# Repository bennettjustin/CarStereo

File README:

Working on writing a detailed README... until then here are some of my ramblings.

## Stereo Project Thoughts
Need to set up organization for project(s)
List of Projects:
- PCBs - group as single repo, ~~single kicad project~~, multiple projects bc messy w/ multiple sheets
	- Audio
	- Main (Raspberry Pi carrier)
	- Power (Car communications)
- CarPlay
	- react-carplay - will be using this initially
	- carplay-rs - in very initial stage of development
- CAD
	- Malibu Stereo faceplate for RPi touchscreen
	- Malibu Stereo adapter for better touchscreen

Order of prioritization
1. PCB - Power
2. PCB - Audio
3. CAD - Faceplate
4. CarPlay (working on getting rpi booting up to react-carplay first)

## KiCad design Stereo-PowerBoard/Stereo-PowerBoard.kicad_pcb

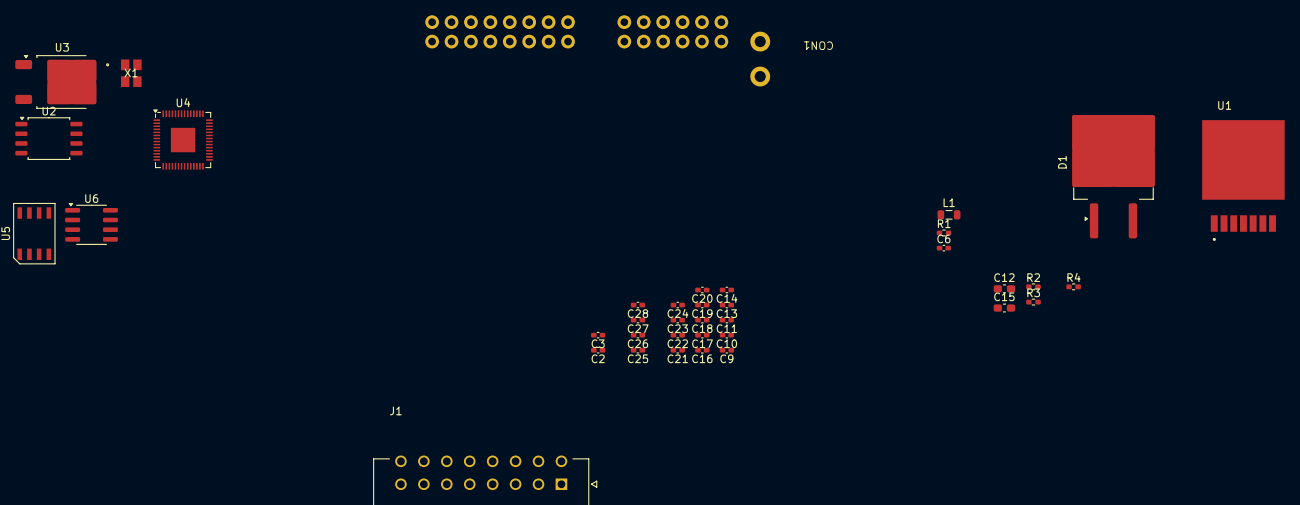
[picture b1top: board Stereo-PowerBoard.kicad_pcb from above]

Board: 2 copper layers, 38 parts (0 on the bottom side), 28 nets, no tracks yet.

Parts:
C2: 1n; C_0402_1005Metric_Pad0.74x0.62mm_HandSolder
C3: 0.01u; C_0402_1005Metric_Pad0.74x0.62mm_HandSolder
C6: 0.47u; C_0402_1005Metric_Pad0.74x0.62mm_HandSolder
C9, C10, C13, C17, C18, C19, C20, C21, C22, C23: 100n; C_0402_1005Metric_Pad0.74x0.62mm_HandSolder
C11, C16: 15p; C_0402_1005Metric_Pad0.74x0.62mm_HandSolder
C12, C15: 10u; C_0603_1608Metric_Pad1.08x0.95mm_HandSolder
C14, C24, C25, C27, C28: 1u; C_0402_1005Metric_Pad0.74x0.62mm_HandSolder
C26: 220p; C_0402_1005Metric_Pad0.74x0.62mm_HandSolder
CON1: Connector Body Harness
D1: 6TQ045S; TO-263-2
J1: 430451600; MOLEX_430451600
L1: 22u; L_0805_2012Metric
R1: 5.6k; R_0402_1005Metric_Pad0.72x0.64mm_HandSolder
R2: R; R_0402_1005Metric_Pad0.72x0.64mm_HandSolder
R3: 1k; R_0402_1005Metric_Pad0.72x0.64mm_HandSolder
R4: 4k7; R_0402_1005Metric_Pad0.72x0.64mm_HandSolder
U1: LM2679SX-5.0_NOPB; VREG_LM2679SX-5.0_NOPB
U2: W25Q32JVSS; SOIC-8_5.23x5.23mm_P1.27mm
U3: NCP1117-3.3_TO252; TO-252-2
U4: RP2040; QFN-56-1EP_7x7mm_P0.4mm_EP3.2x3.2mm
U5: TLIN1027; SOIC-8
U6: TJA1051T-3; SOIC-8_3.9x4.9mm_P1.27mm
X1: ABM8-272-T3; ABM8-272-T3_ABR

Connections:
+1V1: C9.1, C13.1, C14.1, U4.23 (DVDD), U4.45 (VREG_VOUT), U4.50 (DVDD)
+3V3: C10.1, C15.1, C17.1, C18.1, C19.1, C20.1, C21.1, C22.1, C23.1, C24.1, C28.1, R2.1, R4.1, U2.8 (VCC), U3.2 (VO), U4.1 (IOVDD), U4.10 (IOVDD), U4.22 (IOVDD), U4.33 (IOVDD), U4.42 (IOVDD), U4.43 (ADC_AVDD), U4.44 (VREG_IN), U4.48 (USB_VDD), U4.49 (IOVDD), U6.5 (VIO)
+BATT: C6.1, C25.1, CON1.X1.1 (V_BAT), U1.2 (INPUT), U5.7 (VSUP)
GMLAN: CON1.X1.9 (GMLAN), CON1.X1.10 (GMLAN), U6.7 (CANH)
GND: C2.2, C6.2, C9.2, C10.2, C11.2, C12.2, C13.2, C14.2, C15.2, C16.2, C17.2, C18.2, C19.2, C20.2, C21.2, C22.2, C23.2, C24.2, C25.2, C26.2, C27.2, C28.2, CON1.X1.8 (GND), D1.2 (A), R1.2, U1.4 (GND), U1.8 (DAP), U2.4 (GND), U3.1 (GND), U4.19 (TESTEN), U4.57 (GND), U5.5 (GND), U6.2 (GND), U6.6 (CANL), X1.2, X1.4
LIN: C26.1, U5.6 (LIN)
LIN_RXD: R4.2, U5.1 (RXD)
unnamed: C16.1, R3.1, X1.3
unnamed: R1.1, U1.5 (CURRENT_ADJUST)
unnamed: C2.1, U1.7 (SS)
QSPI_SCLK: U2.6 (CLK), U4.52 (QSPI_SCLK)
QSPI_SD0: U2.5 (DI(IO0)), U4.53 (QSPI_SD0)
QSPI_SD1: U2.2 (DO(IO1)), U4.55 (QSPI_SD1)
QSPI_SD2: U2.3 (IO2), U4.54 (QSPI_SD2)
QSPI_SD3: U2.7 (IO3), U4.51 (QSPI_SD3)
QSPI_SS: R2.2, U2.1 (~CS), U4.56 (QSPI_SS)
REG_5V_FDBK: C12.1, C27.1, L1.2, U1.3 (CB), U1.6 (FB), U3.3 (VI), U6.3 (VCC)
REG_5V_OUT: C3.2, D1.1 (K), L1.1, U1.1 (SWITCH_OUTPUT)
SPKR_FL+: CON1.X1.7 (SPKR_FL_B), J1.12
SPKR_FL-: CON1.X1.6 (SPKR_FL_A), J1.11
SPKR_FR+: CON1.X1.5 (SPKR_FR_B), J1.10
SPKR_FR-: CON1.X1.4 (SPKR_FR_A), J1.9
SPKR_RL+: CON1.X2.6 (SPKR_RL_B), J1.14
SPKR_RL-: CON1.X2.7 (SPKR_RL_A), J1.13
SPKR_RR+: CON1.X2.4 (SPKR_RR_B), J1.16
SPKR_RR-: CON1.X2.5 (SPKR_RR_A), J1.15
XIN: C11.1, U4.20 (XIN), X1.1
XOUT: R3.2, U4.21 (XOUT)

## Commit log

2024-08-19 Added readme
2024-08-19 Rename README to README.md
